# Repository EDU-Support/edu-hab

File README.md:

edu-hab
=======
The EDUHAB1_Tracker_Code folder contains the latest softeare release fot the EDUHAB Raspberry Pi Board
It has been extensivley tested with Rasbian version January 2014 Kernel version 3.10

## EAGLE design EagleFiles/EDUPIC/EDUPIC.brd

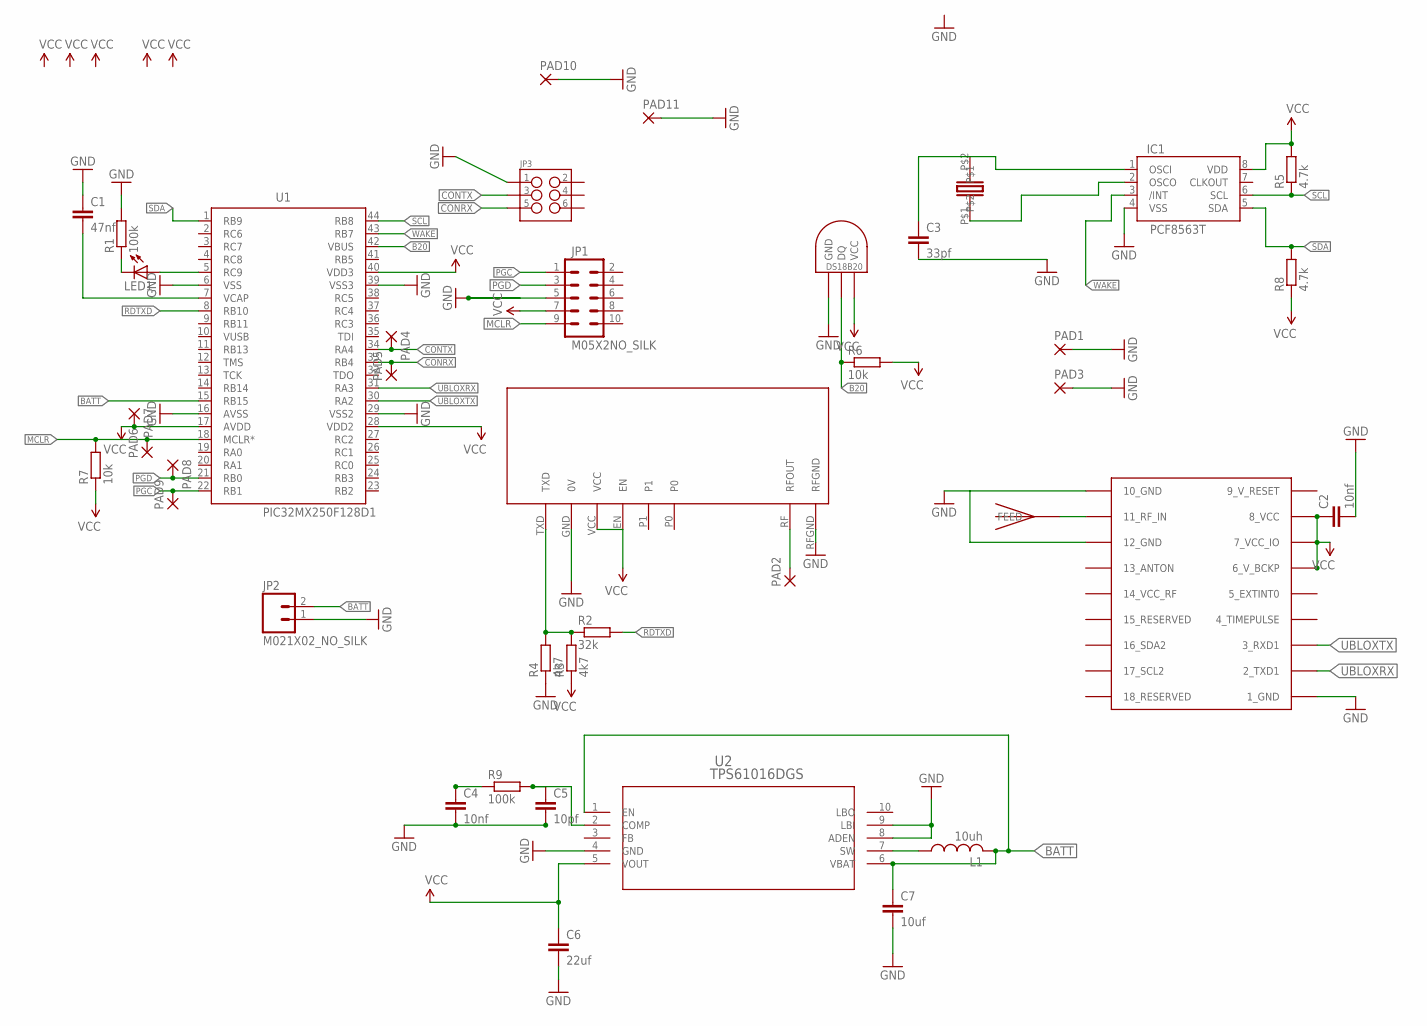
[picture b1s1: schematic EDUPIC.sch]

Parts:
C1: 47nf; C1206
C2: 10nf; C1206
C3: 33pf; C0805
C4: 10nf; C0805
C5: 10pf; C0805
C6: 22uf; C1812
C7: 10uf; C1206
IC1: PCF8563T; SO8
JP1: M05X2NO_SILK; 2X5_NOSILK
JP2: M021X02_NO_SILK; 1X02_NO_SILK
JP3: M03X2NO_SILK; 2X3-NS
L1: 10uh; PIS2816
LED1: LEDCHIP-LED0805; CHIP-LED0805
PAD1, PAD2, PAD3: SMD5; SMD2,54-5,08
PAD4, PAD5, PAD6, PAD7, PAD8, PAD9, PAD10, PAD11: SMD2; SMD1,27-2,54
R1: 100k; R0603
R2: 32k; R1206
R3, R4: 4k7; R0805
R5, R8: 4.7k; R0603
R6, R7: 10k; R0603
R9: 100k; R0805
U1: PIC32MX250F128D1; QFP80P1200X1200X120-44N
U2: TPS61016DGS; DGS10
U$1: RADIOMETRIX-MTX2
U$2: DS1820SOIC; DS18B20_SOIC
U$3: UBLOX_MAX
U$4: JTI_ANTENNA-1575AT43A40
XTAL: 3.2X1.5

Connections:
9_V_RESET: U$3.9_V_RESET
B20: R6.1, U1.42 (VBUS), U$2.DQ
BATT: C7.1, JP2.2, L1.2, U1.15 (RB15), U2.1 (EN), U2.6 (VBAT)
CONRX: JP3.5, PAD5.1, U1.33 (RB4)
CONTX: JP3.3, PAD4.1, U1.34 (RA4)
GND: C1.1, C2.2, C3.2, C4.2, C5.2, C6.2, C7.2, IC1.4 (VSS), JP1.5, JP2.1, JP3.1, PAD1.1, PAD3.1, PAD10.1, PAD11.1, R1.2, R4.1, U1.6 (VSS), U1.16 (AVSS), U1.29 (VSS2), U1.39 (VSS3), U2.4 (GND), U2.8 (ADEN), U2.9 (LBI), U$1.GND (0V), U$1.RFGND, U$2.GND, U$3.1_GND, U$3.10_GND, U$3.12_GND
MCLR: JP1.9, PAD6.1, R7.2, U1.18 (MCLR*)
unnamed: R2.1, R3.2, R4.2, U$1.TXD
unnamed: LED1.A, U1.5 (RC9)
unnamed: U$3.11_RF_IN, U$4.FEED
unnamed: IC1.2 (OSCO), XTAL.P$1
unnamed: PAD2.1, U$1.RF (RFOUT)
unnamed: LED1.C, R1.1
unnamed: C3.1, IC1.1 (OSCI), XTAL.P$2
unnamed: L1.1, U2.7 (SW)
unnamed: C4.1, R9.1
unnamed: C5.1, R9.2, U2.2 (COMP)
unnamed: C1.2, U1.7 (VCAP)
PGC: JP1.1, PAD9.1, U1.22 (RB1)
PGD: JP1.3, PAD8.1, U1.21 (RB0)
RDTXD: R2.2, U1.8 (RB10)
SCL: IC1.6 (SCL), R5.1, U1.44 (RB8)
SDA: IC1.5 (SDA), R8.2, U1.1 (RB9)
UBLOXRX: U1.31 (RA3), U$3.2_TXD1
UBLOXTX: U1.30 (RA2), U$3.3_RXD1
VCC: C2.1, C6.1, IC1.8 (VDD), JP1.7, PAD7.1, R3.1, R5.2, R6.2, R7.1, R8.1, U1.17 (AVDD), U1.28 (VDD2), U1.40 (VDD3), U2.5 (VOUT), U$1.EN, U$1.VCC, U$2.VCC, U$3.6_V_BCKP, U$3.7_VCC_IO, U$3.8_VCC
WAKE: IC1.3 (/INT), U1.43 (RB7)

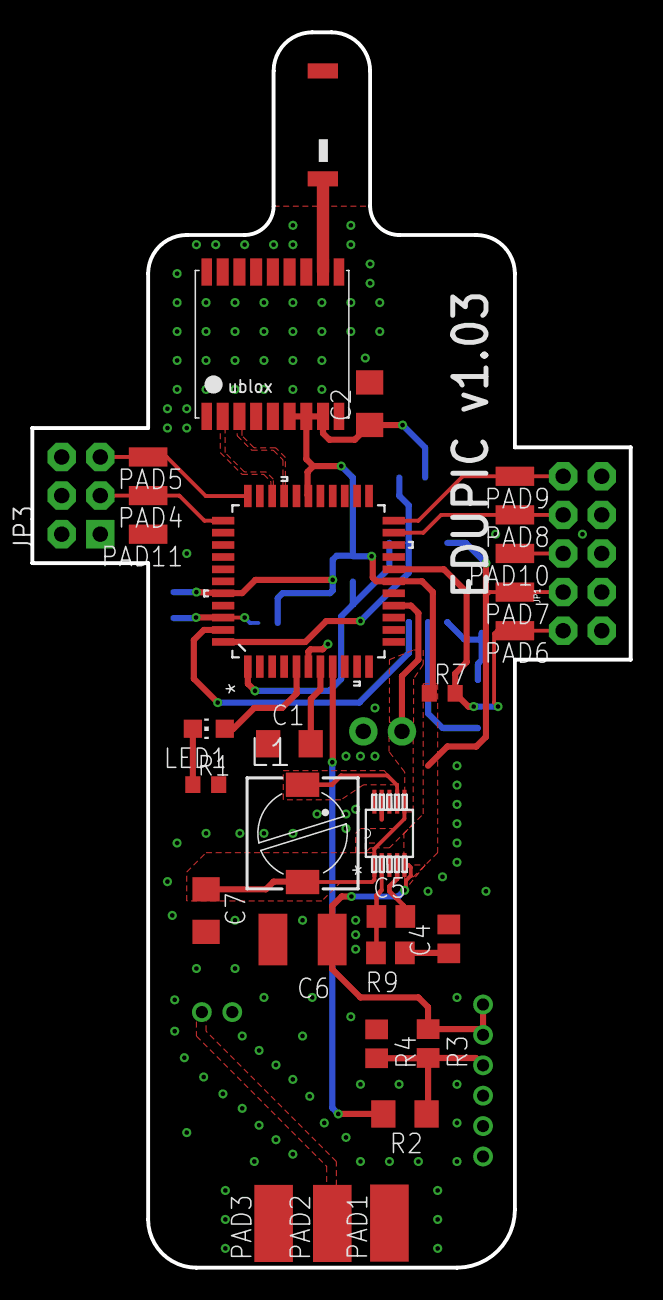
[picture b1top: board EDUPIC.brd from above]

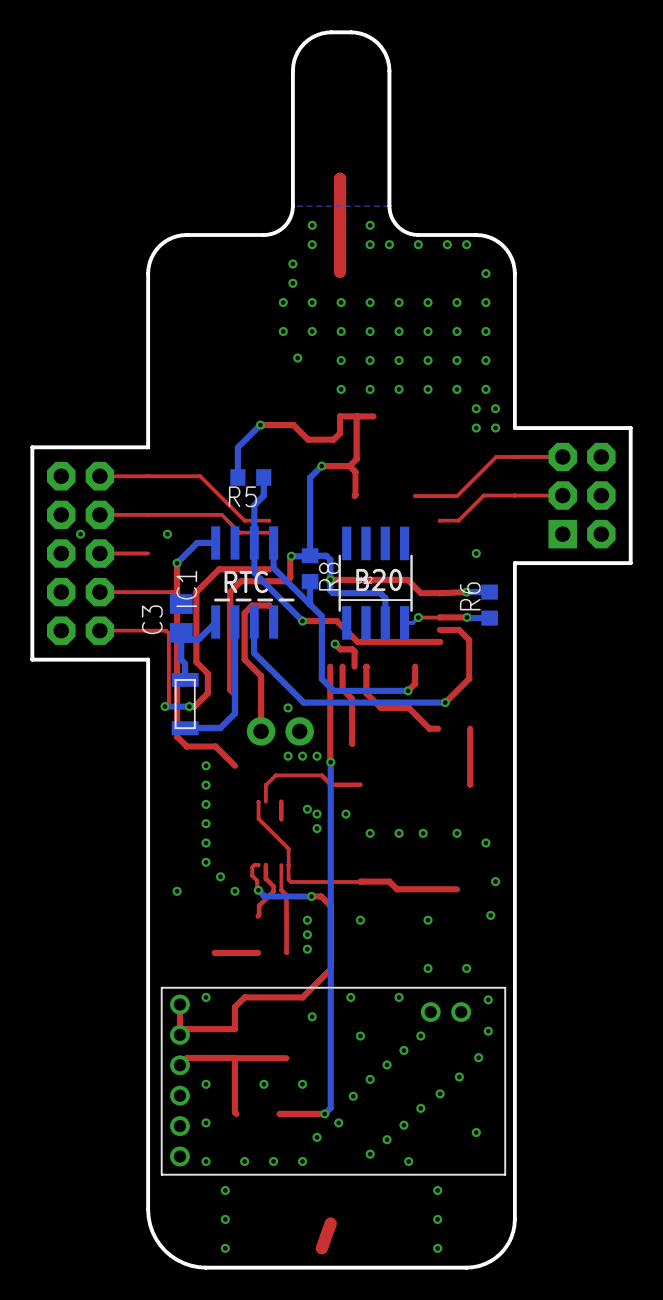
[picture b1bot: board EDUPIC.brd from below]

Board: 2 copper layers, 39.4 x 81.3 mm, 40 parts (8 on the bottom side), 26 nets.

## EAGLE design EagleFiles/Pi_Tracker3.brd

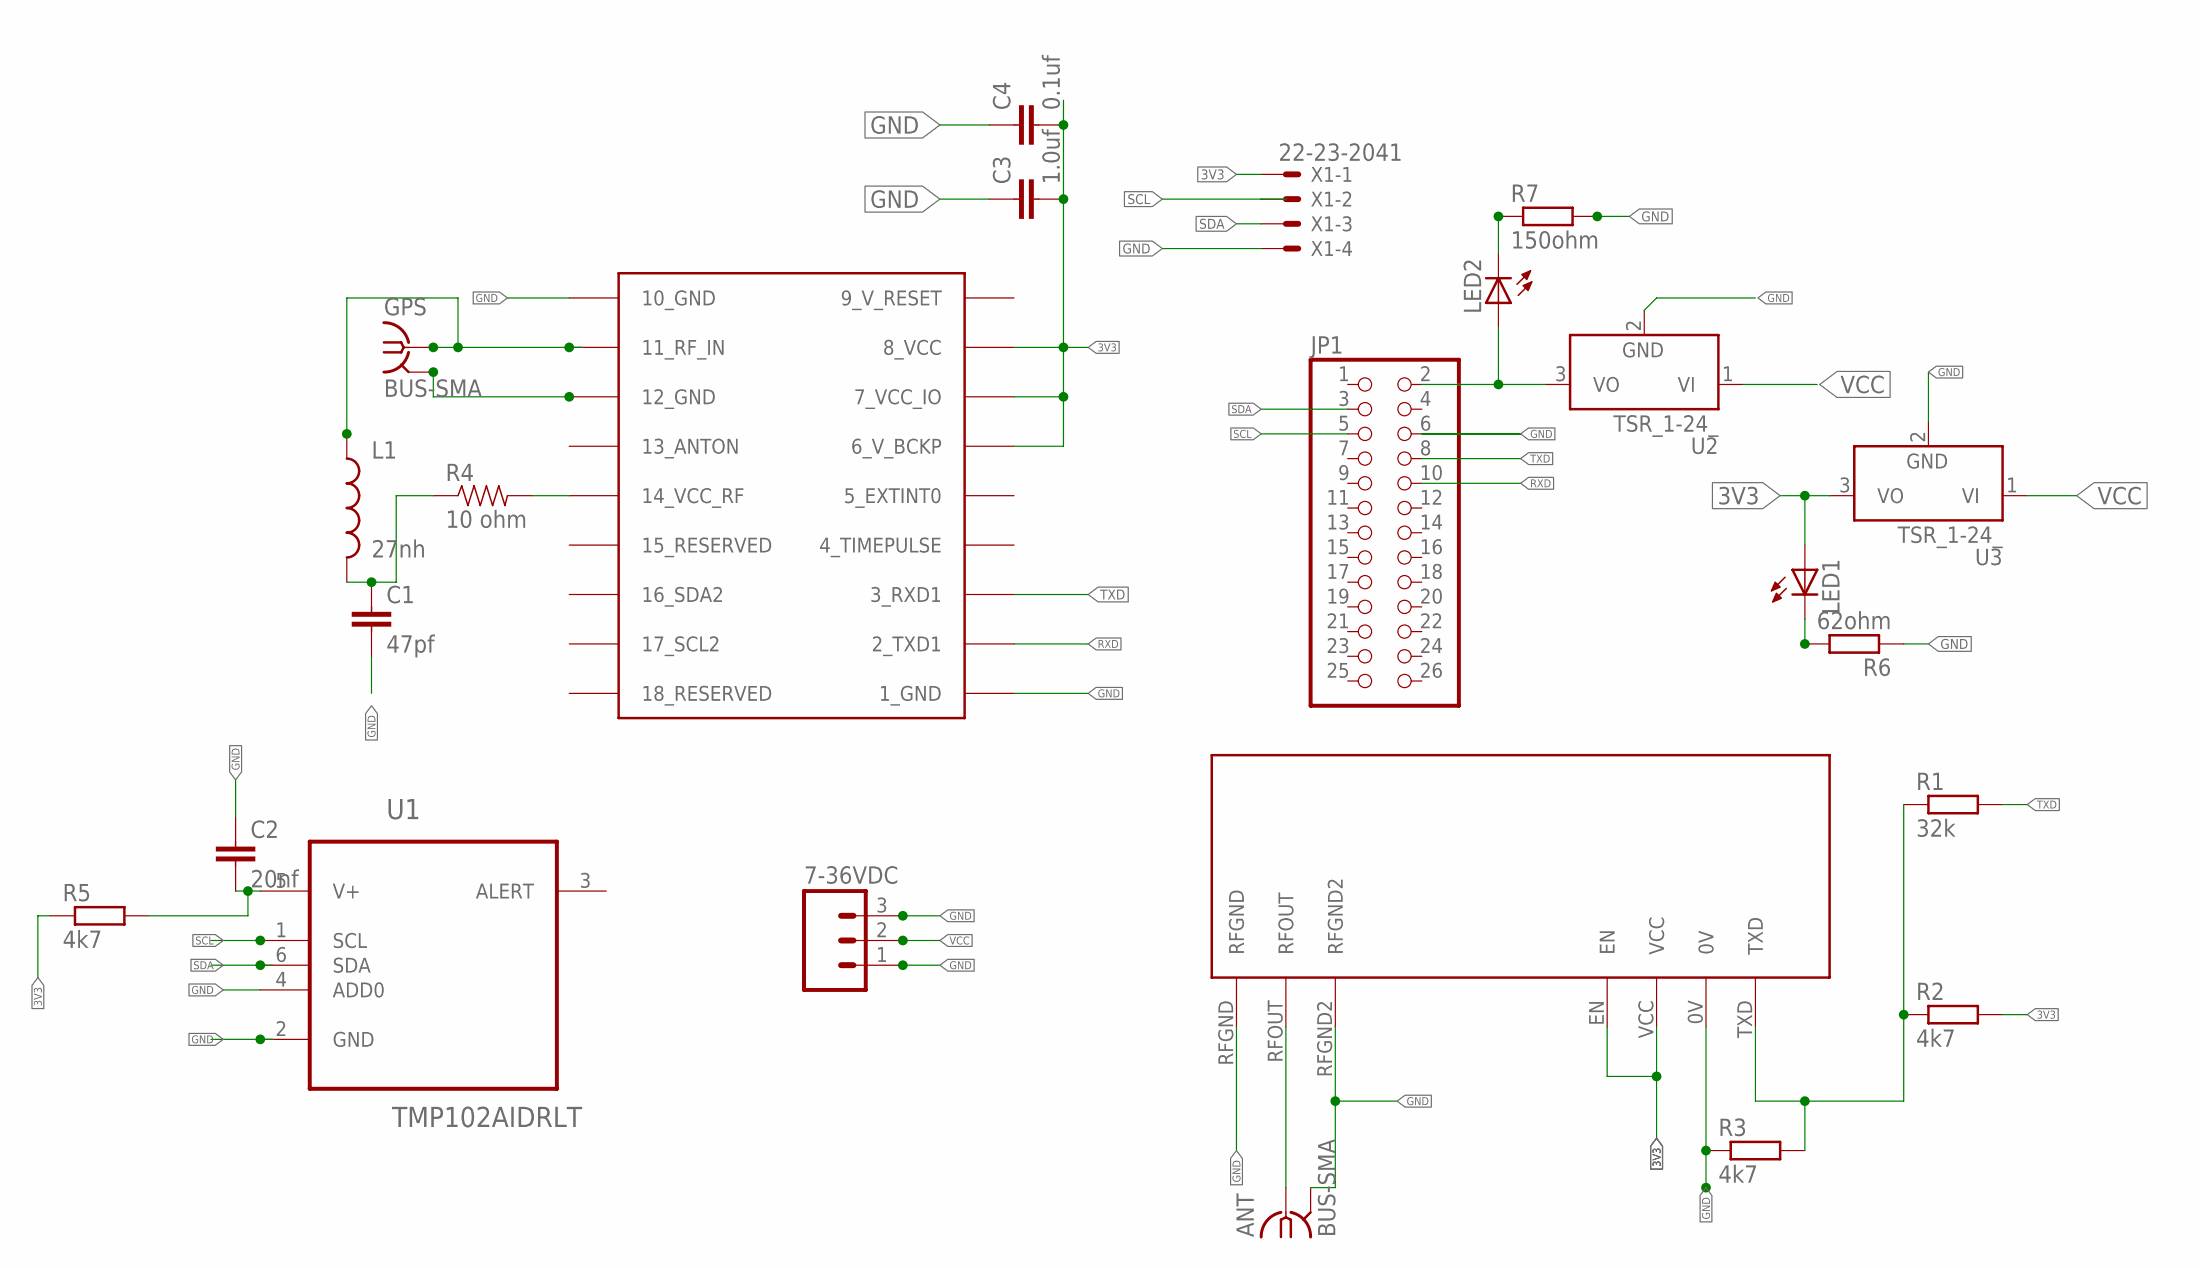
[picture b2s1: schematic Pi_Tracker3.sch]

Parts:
7-36VDC: M03PTH; 1X03
ANT: BUS-SMA
C1: 47pf; 0603-CAP
C2: 20nf; C0603
C3: 1.0uf; C0603
C4: 0.1uf; C0603
GPS: BUS-SMA
JP1: PINHD-2X13; 2X13
L1: 27nh; 0603
LED1, LED2: LEDSML0603; SML0603
R1: 32k; R0603
R2, R3, R5: 4k7; R0603
R4: 10 ohm; 0603-RES
R6: 62ohm; R0603
R7: 150ohm; R0603
U1: TMP102AIDRLT; SOT50P160X60-6N
U2, U3: TSR_1-24_; TSR-1
U$1: NTX2
U$2: UBLOX_MAX
X1: 22-23-2041

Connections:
3V3: C2.2, C3.2, C4.2, LED1.A, R2.2, R5.1, R5.2, U1.5 (V+), U3.3 (VO), U$1.EN, U$1.VCC, U$2.6_V_BCKP, U$2.7_VCC_IO, U$2.8_VCC, X1.1
9_V_RESET: U$2.9_V_RESET
GND: 7-36VDC.1, 7-36VDC.3, ANT.2 (GND), ANT.3 (GND), ANT.4 (GND), ANT.5 (GND), C1.2, C2.1, C3.1, C4.1, GPS.2 (GND), GPS.3 (GND), GPS.4 (GND), GPS.5 (GND), JP1.6, R3.1, R6.1, R7.2, U1.2 (GND), U1.4 (ADD0), U2.2 (GND), U3.2 (GND), U$1.0V, U$1.RFGND, U$1.RFGND2, U$2.1_GND, U$2.10_GND, U$2.12_GND, X1.4
unnamed: R4.2, U$2.14_VCC_RF
unnamed: C1.1, L1.2, R4.1
unnamed: R1.1, R2.1, R3.2, U$1.TXD
unnamed: JP1.2, LED2.A, U2.3 (VO)
unnamed: LED1.C, R6.2
unnamed: ANT.1, U$1.RFOUT
unnamed: LED2.C, R7.1
unnamed: GPS.1, L1.1, U$2.11_RF_IN
RXD: JP1.10, U$2.2_TXD1
SCL: JP1.5, U1.1 (SCL), X1.2
SDA: JP1.3, U1.6 (SDA), X1.3
TXD: JP1.8, R1.2, U$2.3_RXD1
VCC: 7-36VDC.2, U2.1 (VI), U3.1 (VI)

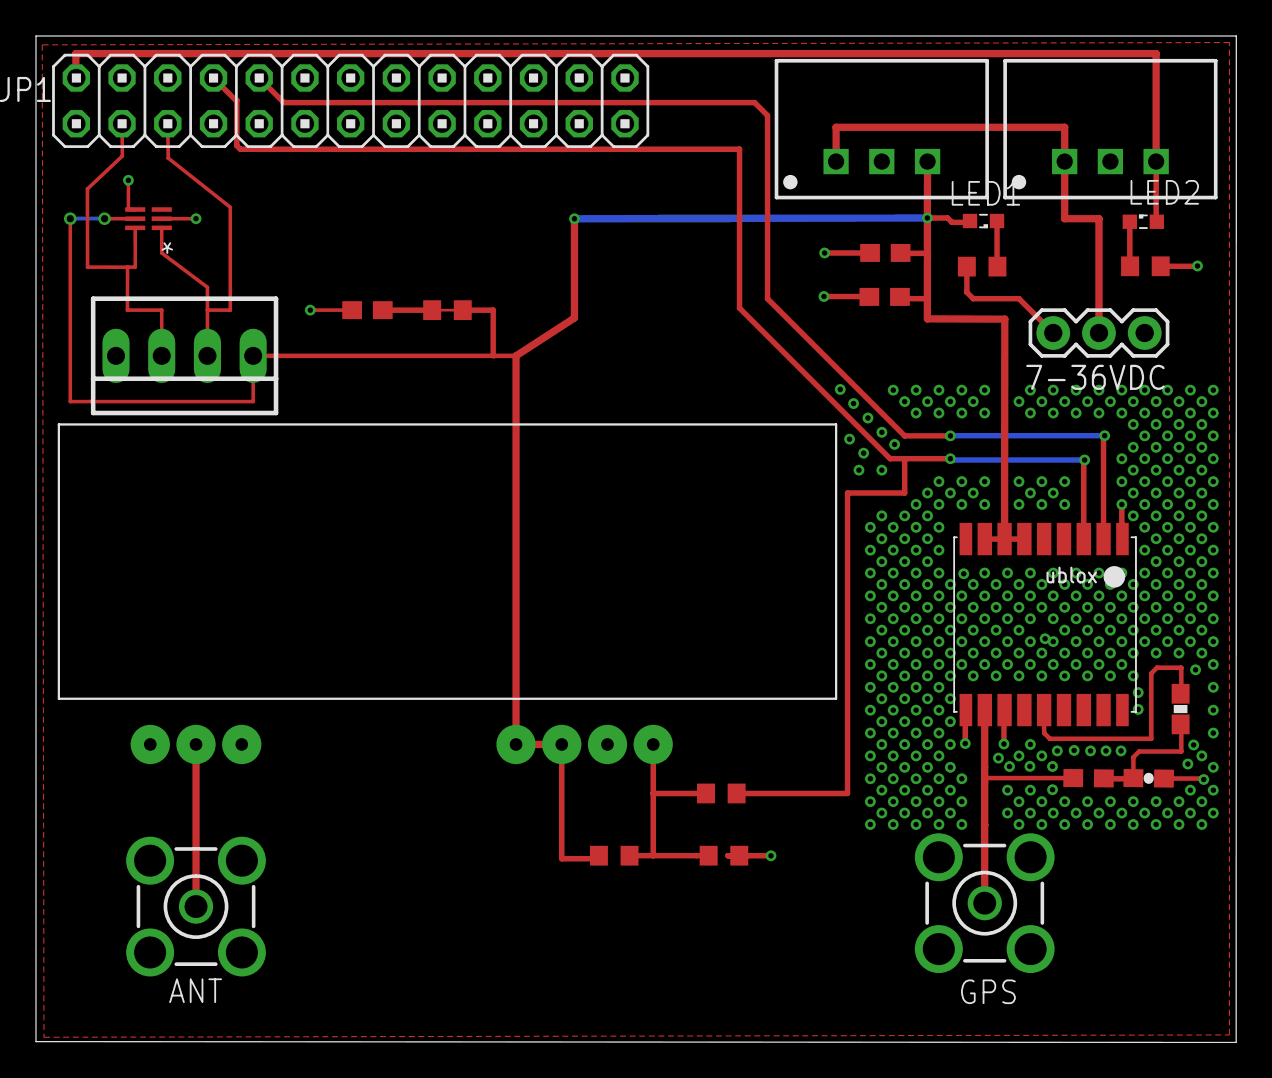
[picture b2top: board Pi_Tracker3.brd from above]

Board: 2 copper layers, 66.7 x 55.9 mm, 24 parts (0 on the bottom side), 15 nets.

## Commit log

2014-03-05 Create tracker4
2014-03-06 Create Pi_Tracker1
2014-03-06 Rename Pi_Tracker1 to Pi_Tracker1.brd
2014-03-20 Create eduhab_v1.py
    Added Sensors
    TMP102 i2c address 48
    BMP085 i2c address 77
    DS18B20 GPIO 4
    DHT22 GPIO 17
    And -p switch to enable timelapse.py
2014-04-06 Create eduhab_v3
2014-05-27 Create Testcode

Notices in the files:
parts and their libraries:
SparkFun-Connectors: Licensing: Creative Commons ShareAlike 4.0 International - https://creativecommons.org/licenses/by-sa/4.0
